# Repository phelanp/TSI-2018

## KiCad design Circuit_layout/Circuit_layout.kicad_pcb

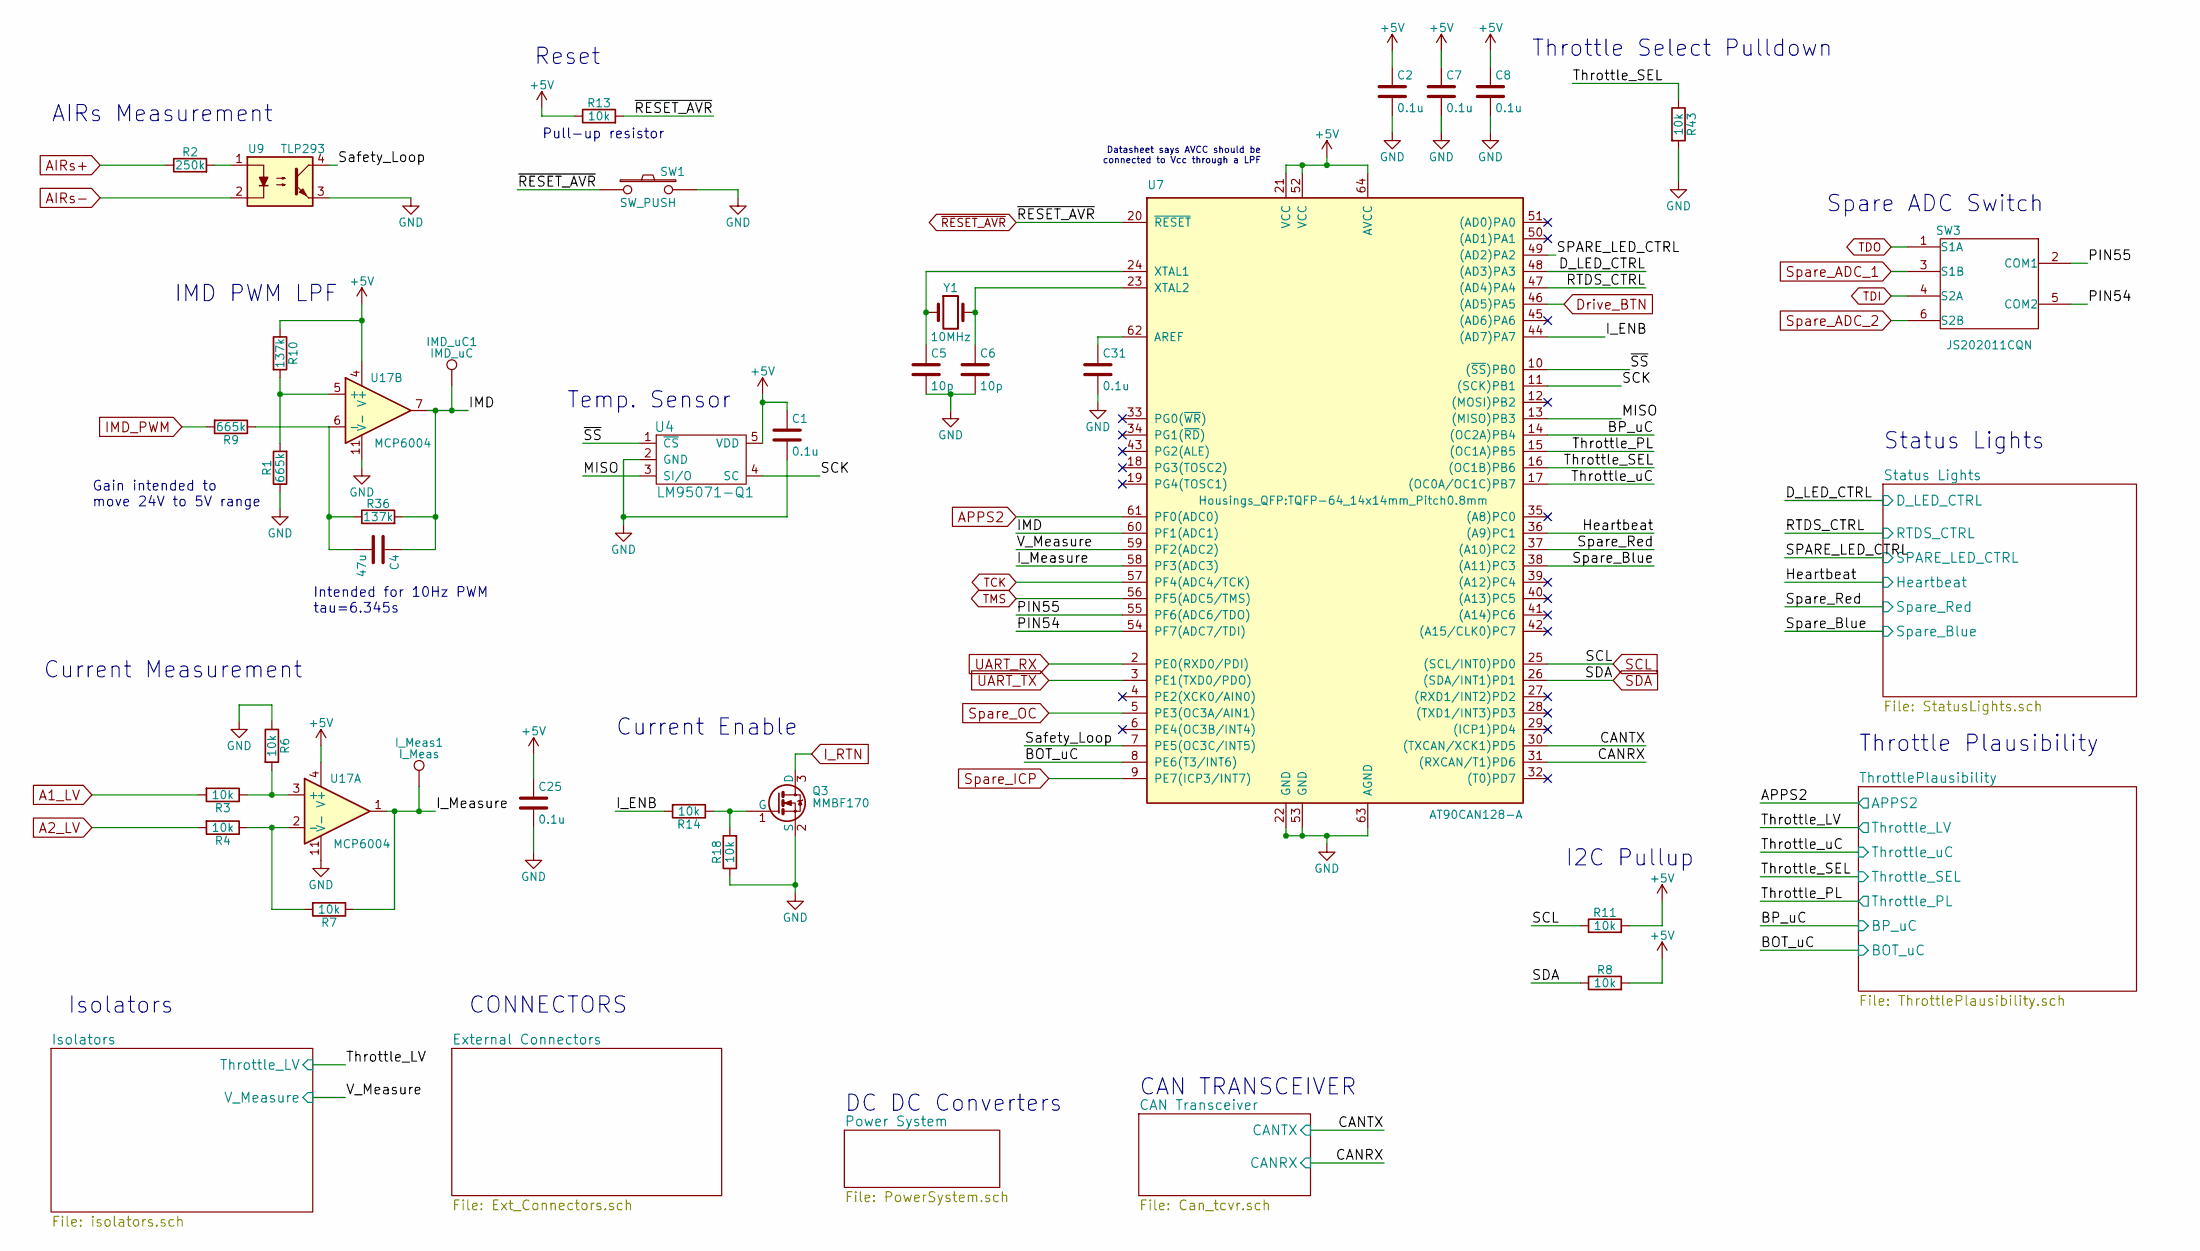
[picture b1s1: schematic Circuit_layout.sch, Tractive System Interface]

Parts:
C1, C2, C7, C8, C25, C31: 0.1u; C_0805_HandSoldering; Digikey P/N 399-1168-1-ND
C4: 47u; C_1210_HandSoldering; Digikey P/N 490-6538-1-ND
C5, C6: 10p; C_0805_HandSoldering; DigiKey P/N 399-1108-1-ND
IMD_uC1: IMD_uC; Measurement_Point_Round-SMD-Pad_Big
I_Meas1: I_Meas; Measurement_Point_Round-SMD-Pad_Big
Q3: MMBF170; SOT-23; Digikey P/N MMBF170CT-ND
R1, R9: 665k; R_0805_HandSoldering; DigiKey P/N P665KCCT-ND
R2: 250k; R_0805_HandSoldering; DigiKey P/N P249KCCT-ND
R3, R4, R6, R7, R8, R11, R13, R14, R18, R43: 10k; R_0805_HandSoldering; DigiKey P/N P10.0KCCT-ND
R10, R36: 137k; R_0805_HandSoldering; DigiKey P/N P137KCCT-ND
SW1: SW_PUSH; SW_RACON_8; DigiKey P/N 1715-1676-1-ND
SW3: JS202011CQN; CK_DPDT_Switch; DigiKey P/N 401-2001-ND
U4: LM95071-Q1; SOT-23-5_HandSoldering; DigiKey P/N 296-40259-1-ND
U7: AT90CAN128-A; TQFP-64_14x14mm_Pitch0.8mm; DigiKey P/N AT90CAN128-16AURCT-ND
U9: TLP293; SOP-4_4.4x2.8mm_Pitch1.27mm; DigiKey P/N TLP293(GB-TPLECT-ND
U17: MCP6004; SOIC-14_3.9x8.7mm_Pitch1.27mm; Digikey P/N MCP6004T-I/SLCT-ND
Y1: 10MHz; crystal_TXC_7A; DigiKey P/N 887-1741-1-ND

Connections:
+5V: C1.1, C2.1, C7.1, C8.1, C25.1, R8.2, R10.1, R11.2, R13.1, U4.5 (VDD), U7.21 (VCC), U7.52 (VCC), U7.64 (AVCC), U17.4 (V+); also elsewhere on the board
/BP_uC: U7.14 ((OC2A)PB4); also elsewhere on the board
/CANRX: U7.31 ((RXCAN/T1)PD6); also elsewhere on the board
/CANTX: U7.30 ((TXCAN/XCK1)PD5); also elsewhere on the board
/D_LED_CTRL: U7.48 ((AD3)PA3); also elsewhere on the board
/Heartbeat: U7.36 ((A9)PC1); also elsewhere on the board
/IMD: C4.1, IMD_uC1.1, R36.2, U7.60 (PF1(ADC1)), U17.7
/I_ENB: R14.2, U7.44 ((AD7)PA7)
/I_Measure: I_Meas1.1, R7.1, U7.58 (PF3(ADC3)), U17.1
/MISO: U4.3 (SI/O), U7.13 ((MISO)PB3)
/PIN54: SW3.5 (COM2), U7.54 (PF7(ADC7/TDI))
/PIN55: SW3.2 (COM1), U7.55 (PF6(ADC6/TDO))
/RTDS_CTRL: U7.47 ((AD4)PA4); also elsewhere on the board
/SCK: U4.4 (SC), U7.11 ((SCK)PB1)
/SPARE_LED_CTRL: U7.49 ((AD2)PA2); also elsewhere on the board
/Safety_Loop: U7.7 (PE5(OC3C/INT5)), U9.4
/Spare_Blue: U7.38 ((A11)PC3); also elsewhere on the board
/Spare_Red: U7.37 ((A10)PC2); also elsewhere on the board
/Throttle_PL: U7.15 ((OC1A)PB5); also elsewhere on the board
/Throttle_SEL: R43.1, U7.16 ((OC1B)PB6); also elsewhere on the board
/Throttle_uC: U7.17 ((OC0A/OC1C)PB7); also elsewhere on the board
/V_Measure: U7.59 (PF2(ADC2)); also elsewhere on the board
/~SS: U4.1 (~CS), U7.10 ((~SS~)PB0)
A1_LV: R3.2; also elsewhere on the board
A2_LV: R4.2; also elsewhere on the board
AIRs+: R2.1; also elsewhere on the board
AIRs-: U9.2; also elsewhere on the board
APPS2: U7.61 (PF0(ADC0)); also elsewhere on the board
CH_GND: C1.2, C2.2, C5.2, C6.2, C7.2, C8.2, C25.2, C31.2, Q3.2 (S), R1.1, R6.1, R18.1, R43.2, SW1.2, U4.2 (GND), U7.22 (GND), U7.53 (GND), U7.63 (AGND), U9.3, U17.11 (V-); also elsewhere on the board
Drive_BTN: U7.46 ((AD5)PA5); also elsewhere on the board
IMD_PWM: R9.2; also elsewhere on the board
I_RTN: Q3.3 (D); also elsewhere on the board
unnamed: C4.2, R9.1, R36.1, U17.6 (-)
unnamed: C5.1, U7.24 (XTAL1), Y1.1
unnamed: C6.1, U7.23 (XTAL2), Y1.2
unnamed: C31.1, U7.62 (AREF)
unnamed: Q3.1 (G), R14.1, R18.2
unnamed: R1.2, R10.2, U17.5 (+)
unnamed: R2.2, U9.1
unnamed: R3.1, R6.2, U17.3 (+)
unnamed: R4.1, R7.2, U17.2 (-)
SCL: R11.1, U7.25 ((SCL/INT0)PD0); also elsewhere on the board
SDA: R8.1, U7.26 ((SDA/INT1)PD1); also elsewhere on the board
Spare_ADC_1: SW3.3 (S1B); also elsewhere on the board
Spare_ADC_2: SW3.6 (S2B); also elsewhere on the board
Spare_ICP: U7.9 (PE7(ICP3/INT7)); also elsewhere on the board
Spare_OC: U7.5 (PE3(OC3A/AIN1)); also elsewhere on the board
TCK: U7.57 (PF4(ADC4/TCK)); also elsewhere on the board
TDI: SW3.4 (S2A); also elsewhere on the board
TDO: SW3.1 (S1A); also elsewhere on the board
TMS: U7.56 (PF5(ADC5/TMS)); also elsewhere on the board
UART_RX: U7.2 (PE0(RXD0/PDI)); also elsewhere on the board
UART_TX: U7.3 (PE1(TXD0/PDO)); also elsewhere on the board
~RESET_AVR: R13.2, SW1.1, U7.20 (~RESET); also elsewhere on the board

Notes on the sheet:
CONNECTORS
CAN TRANSCEIVER
Current Measurement
IMD PWM LPF
AIRs Measurement
Throttle Plausibility
Status Lights
DC DC Converters
Isolators
Intended for 10Hz PWM tau=6.345s
I2C Pullup
Datasheet says AVCC should be connected to Vcc through a LPF
Pull-up resistor
Reset
Throttle Select Pulldown
Spare ADC Switch
Current Enable
Gain intended to move 24V to 5V range
Temp. Sensor

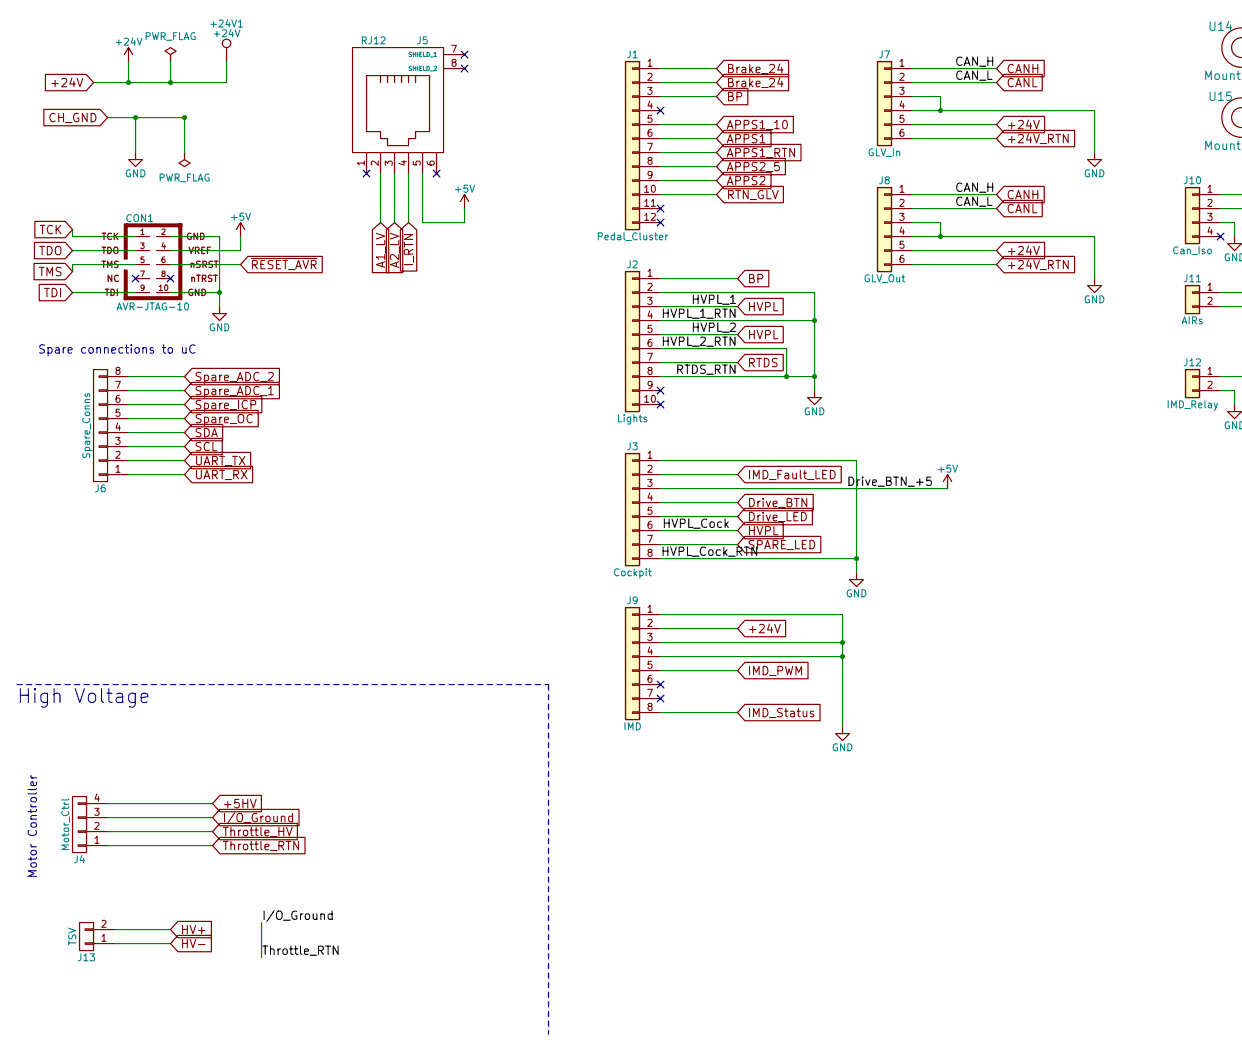
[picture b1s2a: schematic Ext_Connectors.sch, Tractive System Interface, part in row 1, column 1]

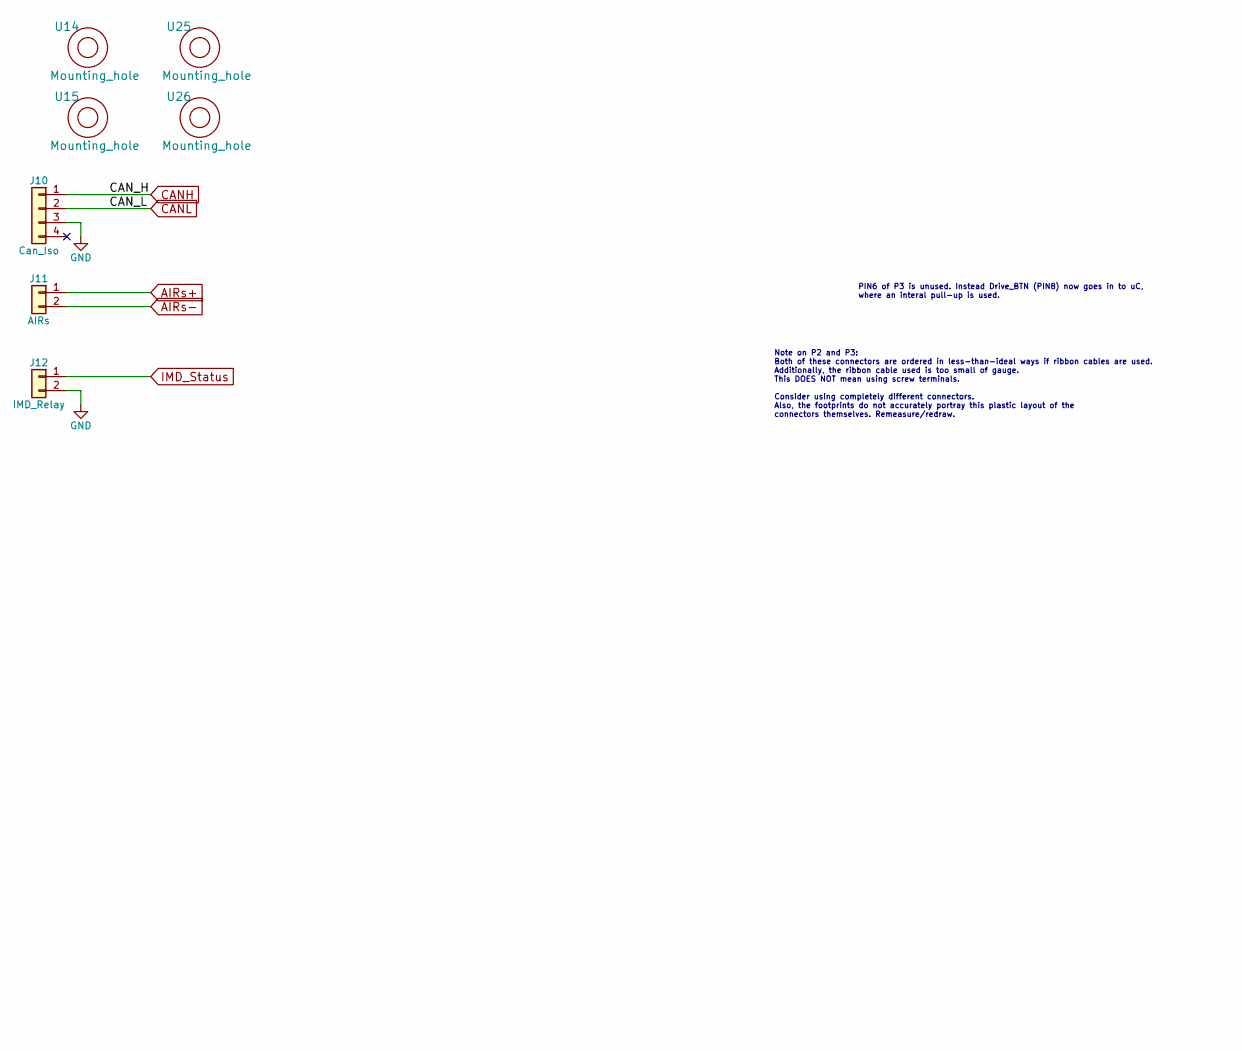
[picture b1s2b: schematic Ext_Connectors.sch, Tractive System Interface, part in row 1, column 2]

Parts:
+24V1: +24V; Measurement_Point_Round-SMD-Pad_Big
CON1: AVR-JTAG-10; JTAG; DigiKey P/N 609-4054-ND
J1: Pedal_Cluster; Molex_MiniFit-JR-5556-12A_2x06x4.20mm_Straight
J2: Lights; Molex_MiniFit-JR-5556-10A_2x05x4.20mm_Straight
J3: Cockpit; Molex_MiniFit-JR-5556-08A_2x04x4.20mm_Straight
J4: Motor_Ctrl; Molex_4x1_2.54mm; DigiKey P/N WM4802-ND
J5: RJ12; MOLEX_RJ11; DigiKey P/N WM3789CT-ND
J6: Spare_Conns; Molex_8x1_2.54mm; DigiKey P/N WM4128-ND
J7: GLV_In; Molex_MiniFit-JR-5556-06A_2x03x4.20mm_Straight
J8: GLV_Out; Molex_MiniFit-JR-5556-06A_2x03x4.20mm_Straight
J9: IMD; IMD_Header
J10: Can_Iso; Molex_MiniFit-JR-5556-04A_2x02x4.20mm_Straight
J11: AIRs; Molex_MiniFit-JR-5556-02A_2x01x4.20mm_Straight
J12: IMD_Relay; Molex_MiniFit-JR-5556-02A_2x01x4.20mm_Straight
J13: TSV; AMPCONN_2; DigiKey P/N A113980-ND
U14, U15, U25, U26: Mounting_hole; MountingHole_3.5mm_Pad

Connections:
+5HV: J4.4; also elsewhere on the board
+5V: CON1.4, J3.3, J5.5; also elsewhere on the board
+24V: +24V1.1, J1.1, J1.2, J7.5, J8.5, J9.2; also elsewhere on the board
+24V_RTN: J7.6, J8.6; also elsewhere on the board
A1_LV: J5.2; also elsewhere on the board
A2_LV: J5.3; also elsewhere on the board
AIRs+: J11.1; also elsewhere on the board
AIRs-: J11.2; also elsewhere on the board
APPS1: J1.6; also elsewhere on the board
APPS1_10: J1.5; also elsewhere on the board
APPS1_RTN: J1.7; also elsewhere on the board
APPS2: J1.9; also elsewhere on the board
APPS2_5: J1.8; also elsewhere on the board
BP: J1.3, J2.1; also elsewhere on the board
CANH: J7.1, J8.1, J10.1; also elsewhere on the board
CANL: J7.2, J8.2, J10.2; also elsewhere on the board
CH_GND: CON1.2, CON1.10, J1.10, J2.2, J2.4, J2.6, J2.8, J3.1, J3.8, J7.3, J7.4, J8.3, J8.4, J9.1, J9.3, J9.4, J10.3, J12.2; also elsewhere on the board
Drive_BTN: J3.4; also elsewhere on the board
Drive_LED: J3.5; also elsewhere on the board
HV+: J13.2; also elsewhere on the board
HV-: J13.1; also elsewhere on the board
HVPL: J2.3, J2.5, J3.6; also elsewhere on the board
I/O_Ground: J4.1, J4.3; also elsewhere on the board
IMD_Fault_LED: J3.2; also elsewhere on the board
IMD_PWM: J9.5; also elsewhere on the board
IMD_Status: J9.8, J12.1; also elsewhere on the board
I_RTN: J5.4; also elsewhere on the board
RTDS: J2.7; also elsewhere on the board
SCL: J6.3; also elsewhere on the board
SDA: J6.4; also elsewhere on the board
SPARE_LED: J3.7; also elsewhere on the board
Spare_ADC_1: J6.7; also elsewhere on the board
Spare_ADC_2: J6.8; also elsewhere on the board
Spare_ICP: J6.6; also elsewhere on the board
Spare_OC: J6.5; also elsewhere on the board
TCK: CON1.1; also elsewhere on the board
TDI: CON1.9; also elsewhere on the board
TDO: CON1.3; also elsewhere on the board
TMS: CON1.5; also elsewhere on the board
Throttle_HV: J4.2; also elsewhere on the board
UART_RX: J6.1; also elsewhere on the board
UART_TX: J6.2; also elsewhere on the board
~RESET_AVR: CON1.6; also elsewhere on the board

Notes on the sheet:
Motor Controller
High Voltage
Spare connections to uC
PIN6 of P3 is unused. Instead Drive_BTN (PIN8) now goes in to uC, where an interal pull-up is used.
Note on P2 and P3: Both of these connectors are ordered in less-than-ideal ways if ribbon cables are used. Additionally, the ribbon cable used is too small of gauge. This DOES NOT mean using screw terminals. Consider using completely different connectors. Also, the footprints do not accurately port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

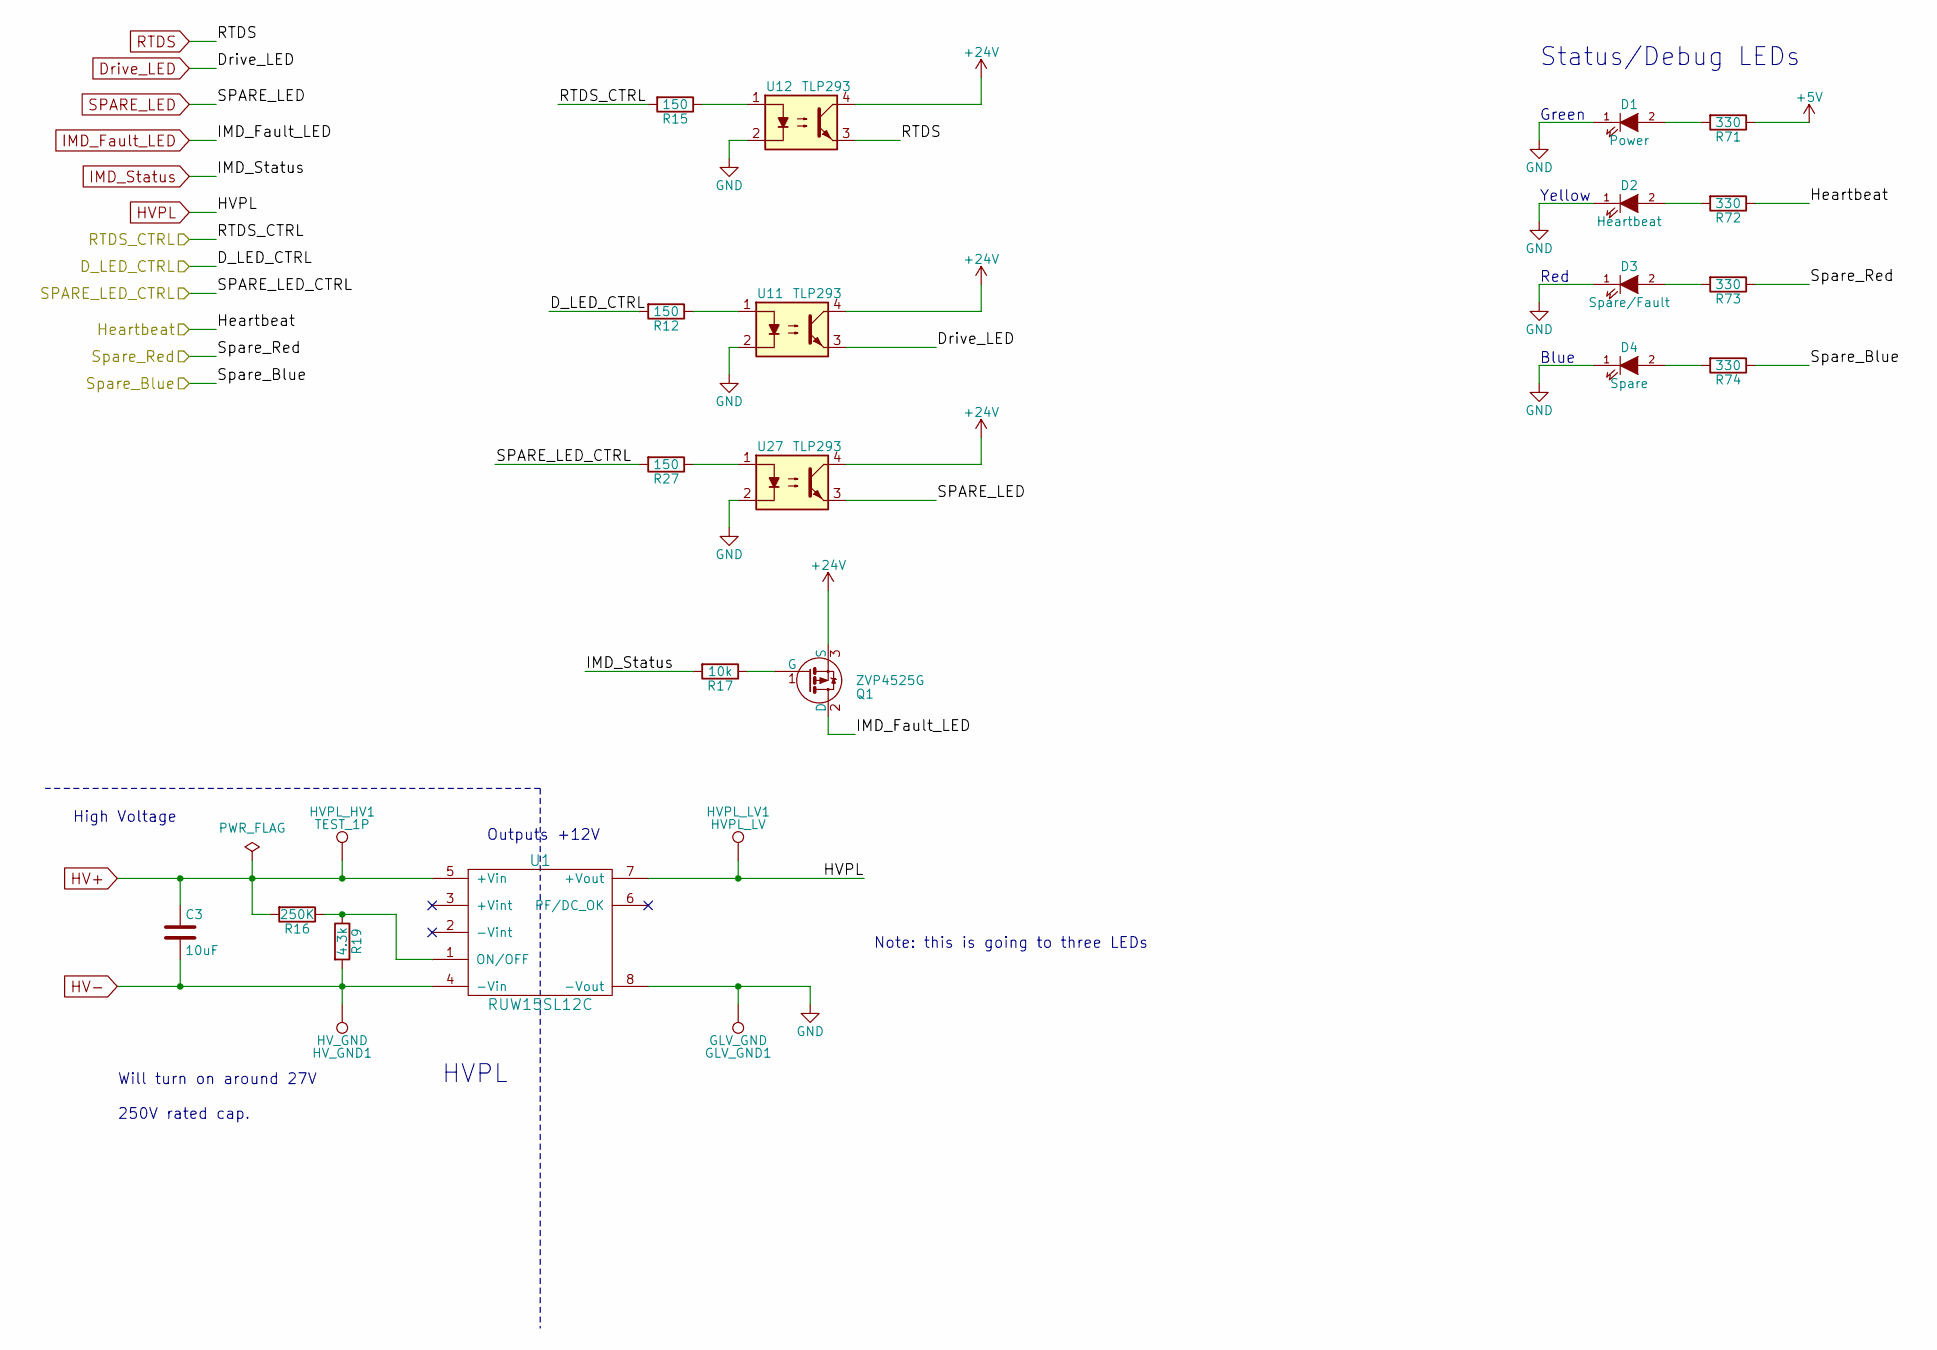
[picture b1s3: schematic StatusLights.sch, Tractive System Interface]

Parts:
C3: 10uF; CP_Radial_D10.0mm_P5.00mm; DigiKey P/N 490-3550-1-ND
D1: Power; LED_0805; DigiKey P/N 475-1410-1-ND
D2: Heartbeat; LED_0805; DigiKey P/N 475-2560-1-ND
D3: Spare/Fault; LED_0805; DigiKey P/N 475-1278-1-ND
D4: Spare; LED_0805; DigiKey P/N 516-1445-1-ND
GLV_GND1: GLV_GND; Measurement_Point_Square-SMD-Pad_Big
HVPL_HV1: TEST_1P; Measurement_Point_Round-SMD-Pad_Big
HVPL_LV1: HVPL_LV; Measurement_Point_Round-SMD-Pad_Big
HV_GND1: HV_GND; Measurement_Point_Square-SMD-Pad_Big
Q1: ZVP4525G; SOT-223-3Lead_TabPin2; DigiKey P/N ZVP4525GCT-ND
R12, R15, R27: 150; R_0805_HandSoldering; DigiKey P/N 311-150CRCT-ND
R16: 250K; R_0805_HandSoldering
R17: 10k; R_0805_HandSoldering; DigiKey P/N P10.0KCCT-ND
R19: 4.3k; R_0805_HandSoldering
R71, R72, R73, R74: 330; R_0805_HandSoldering; DigiKey P/N P330CCT-ND
U1: RUW15SL12C; RUW15
U11, U12, U27: TLP293; SOP-4_4.4x2.8mm_Pitch1.27mm; DigiKey P/N TLP293(GB-TPLECT-ND

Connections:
+5V: R71.1; also elsewhere on the board
+24V: Q1.3 (S), U11.4, U12.4, U27.4; also elsewhere on the board
/D_LED_CTRL: R12.2; also elsewhere on the board
/Heartbeat: R72.1; also elsewhere on the board
/RTDS_CTRL: R15.2; also elsewhere on the board
/SPARE_LED_CTRL: R27.2; also elsewhere on the board
/Spare_Blue: R74.1; also elsewhere on the board
/Spare_Red: R73.1; also elsewhere on the board
CH_GND: D1.1 (K), D2.1 (K), D3.1 (K), D4.1 (K), GLV_GND1.1, U1.8 (-Vout), U11.2, U12.2, U27.2; also elsewhere on the board
Drive_LED: U11.3; also elsewhere on the board
HV+: C3.1, HVPL_HV1.1, R16.2, U1.5 (+Vin); also elsewhere on the board
HV-: C3.2, HV_GND1.1, R19.2, U1.4 (-Vin); also elsewhere on the board
HVPL: HVPL_LV1.1, U1.7 (+Vout); also elsewhere on the board
IMD_Fault_LED: Q1.2 (D); also elsewhere on the board
IMD_Status: R17.2; also elsewhere on the board
unnamed: D1.2 (A), R71.2
unnamed: D2.2 (A), R72.2
unnamed: D3.2 (A), R73.2
unnamed: D4.2 (A), R74.2
unnamed: Q1.1 (G), R17.1
unnamed: R12.1, U11.1
unnamed: R15.1, U12.1
unnamed: R16.1, R19.1, U1.1 (ON/OFF)
unnamed: R27.1, U27.1
RTDS: U12.3; also elsewhere on the board
SPARE_LED: U27.3; also elsewhere on the board

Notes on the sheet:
Green
Yellow
Red
Blue
Status/Debug LEDs
High Voltage
Note: this is going to three LEDs
Outputs +12V
HVPL
Will turn on around 27V 250V rated cap.

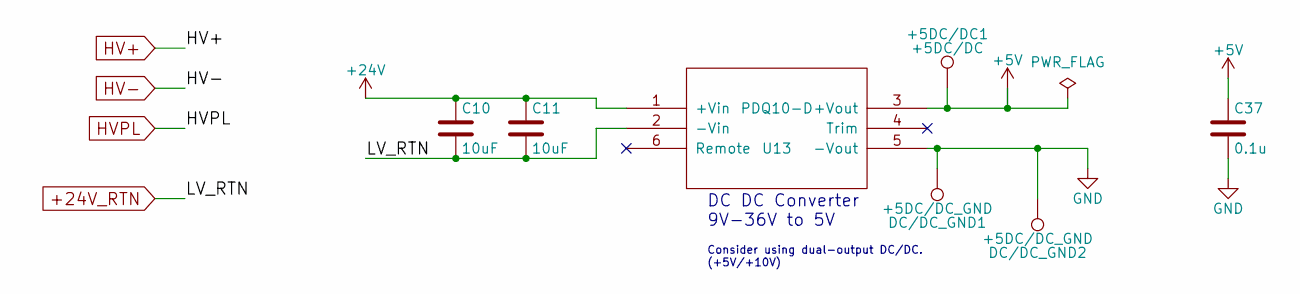
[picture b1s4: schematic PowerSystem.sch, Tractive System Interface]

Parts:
+5DC/DC1: +5DC/DC; trim_pot
C10, C11: 10uF; C_0805_HandSoldering; DigiKey P/N 490-10515-1-ND
C37: 0.1u; C_0805_HandSoldering; Digikey P/N 399-1168-1-ND
DC/DC_GND1, DC/DC_GND2: +5DC/DC_GND; Measurement_Point_Square-SMD-Pad_Big
U13: PDQ10-D; PDQ_DCDC; DigiKey P/N 102-3865-ND

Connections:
+5V: +5DC/DC1.1, C37.1, U13.3 (+Vout); also elsewhere on the board
+24V: C10.1, C11.1, U13.1 (+Vin); also elsewhere on the board
+24V_RTN: C10.2, C11.2, U13.2 (-Vin); also elsewhere on the board
CH_GND: C37.2, DC/DC_GND1.1, DC/DC_GND2.1, U13.5 (-Vout); also elsewhere on the board

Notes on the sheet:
DC DC Converter 9V-36V to 5V
Consider using dual-output DC/DC. (+5V/+10V)

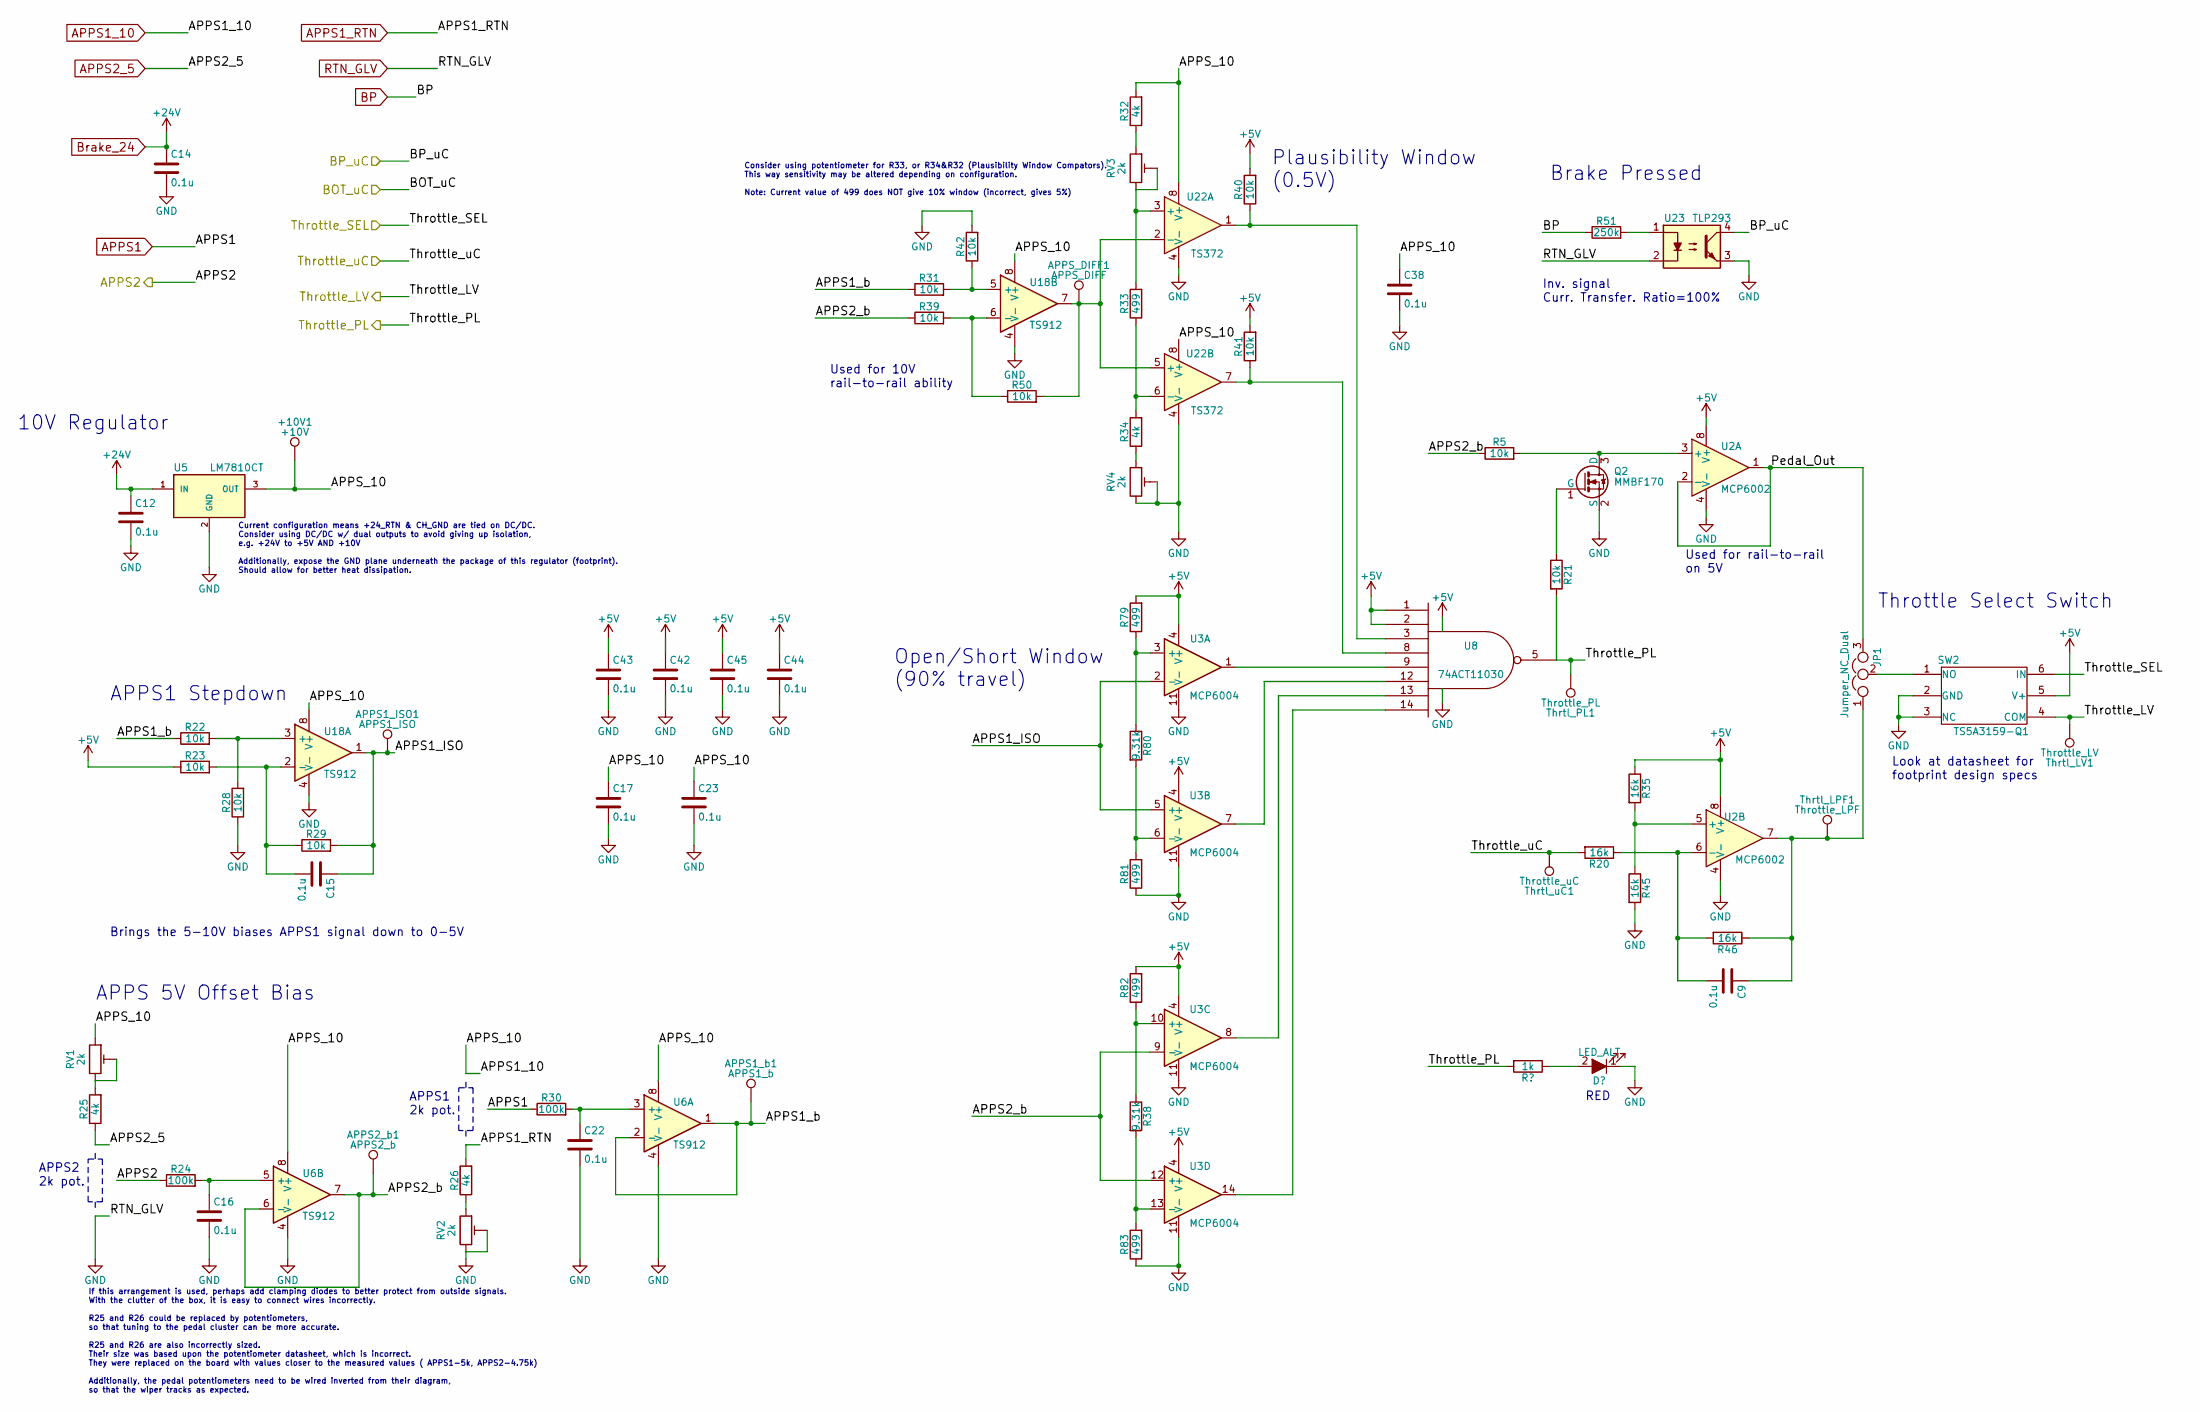
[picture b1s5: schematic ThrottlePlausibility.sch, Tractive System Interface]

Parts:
+10V1: +10V; Measurement_Point_Round-SMD-Pad_Big
APPS1_ISO1: APPS1_ISO; Measurement_Point_Round-SMD-Pad_Big
APPS1_b1: APPS1_b; Measurement_Point_Round-SMD-Pad_Big
APPS2_b1: APPS2_b; Measurement_Point_Round-SMD-Pad_Big
APPS_DIFF1: APPS_DIFF; Measurement_Point_Round-SMD-Pad_Big
C9, C12, C14, C15, C16, C17, C22, C23, C38, C42, C43, C44, C45: 0.1u; C_0805_HandSoldering; Digikey P/N 399-1168-1-ND
JP1: Jumper_NC_Dual; Pin_Header_Straight_1x03_Pitch2.54mm
Q2: MMBF170; SOT-23; Digikey P/N MMBF170CT-ND
R5, R21, R22, R23, R28, R29, R31, R39, R40, R41, R42, R50: 10k; R_0805_HandSoldering; DigiKey P/N P10.0KCCT-ND
R20, R35, R45, R46: 16k; R_0805_HandSoldering; DigiKey P/N P10.0KCCT-ND
R24, R30: 100k; R_0805_HandSoldering; DigiKey P/N P100KCCT-ND
R25, R26: 4k; R_0805_HandSoldering; DigiKey P/N P2.00KCCT-ND
R32, R34: 4k; R_0805_HandSoldering; DigiKey P/N P4.75KCCT-ND
R33, R79, R81, R82, R83: 499; R_0805_HandSoldering; DigiKey P/N P499DACT-ND
R38, R80: 9.31k; R_0805_HandSoldering; Digikey P/N P9.31KCCT-ND
R51: 250k; R_0805_HandSoldering; DigiKey P/N P249KCCT-ND
RV1, RV2, RV3, RV4: 2k; trim_pot
SW2: TS5A3159-Q1; SOT-23-6_Handsoldering; DigiKey P/N 296-39512-1-ND
Thrtl_LPF1: Throttle_LPF; Measurement_Point_Square-SMD-Pad_Big
Thrtl_LV1: Throttle_LV; Measurement_Point_Round-SMD-Pad_Big
Thrtl_PL1: Throttle_PL; Measurement_Point_Round-SMD-Pad_Big
Thrtl_uC1: Throttle_uC; Measurement_Point_Square-SMD-Pad_Big
U2: MCP6002; SOIC-8_3.9x4.9mm_Pitch1.27mm; DigiKey P/N MCP6002T-I/SNCT-ND
U3: MCP6004; SOIC-14_3.9x8.7mm_Pitch1.27mm; Digikey P/N MCP6004T-I/SLCT-ND
U5: LM7810CT; TO-220_Horizontal_Plated_Hole; DigiKey P/N LM7810CT-ND
U6, U18: TS912; SOIC-8_3.9x4.9mm_Pitch1.27mm; DigiKey P/N 497-10252-1-ND
U8: 74ACT11030; SOIC-14_3.9x8.7mm_Pitch1.27mm; Digikey P/N 296-4180-1-ND
U22: TS372; SOIC-8_3.9x4.9mm_Pitch1.27mm; DigiKey P/N 497-2271-1-ND
U23: TLP293; SOP-4_4.4x2.8mm_Pitch1.27mm; DigiKey P/N TLP293(GB-TPLECT-ND

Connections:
+5V: C42.1, C43.1, C44.1, C45.1, R23.1, R35.1, R40.2, R41.2, R79.2, R82.2, SW2.5 (V+), U2.8 (V+), U3.4 (V+), U8.1, U8.2, U8.11 (VCC); also elsewhere on the board
+24V: C12.1, C14.1, U5.1 (IN); also elsewhere on the board
/BP_uC: U23.4; also elsewhere on the board
/ThrottlePlausibility/APPS1_ISO: APPS1_ISO1.1, C15.1, R29.2, U3.2 (-), U3.5 (+), U18.1
/ThrottlePlausibility/APPS1_b: APPS1_b1.1, R22.1, R31.1, U6.1, U6.2 (-)
/ThrottlePlausibility/APPS2_b: APPS2_b1.1, R5.1, R39.1, U3.9 (-), U3.12 (+), U6.6 (-), U6.7
/ThrottlePlausibility/Pedal_Out: JP1.3, U2.1, U2.2 (-)
/Throttle_LV: SW2.4 (COM), Thrtl_LV1.1; also elsewhere on the board
/Throttle_PL: R21.2, Thrtl_PL1.1, U8.5; also elsewhere on the board
/Throttle_SEL: SW2.6 (IN); also elsewhere on the board
/Throttle_uC: R20.2, Thrtl_uC1.1; also elsewhere on the board
APPS1: R30.1; also elsewhere on the board
APPS1_10: +10V1.1, C17.1, C23.1, C38.1, R32.2, RV1.1, U5.3 (OUT), U6.8 (V+), U18.8 (V+), U22.8 (V+); also elsewhere on the board
APPS1_RTN: R26.2; also elsewhere on the board
APPS2: R24.1; also elsewhere on the board
APPS2_5: R25.1; also elsewhere on the board
BP: R51.1; also elsewhere on the board
CH_GND: C12.2, C14.2, C16.2, C17.2, C22.2, C23.2, C38.2, C42.2, C43.2, C44.2, C45.2, Q2.2 (S), R28.1, R42.2, R45.2, R81.1, R83.1, RV2.2, RV2.3, RV4.2, RV4.3, SW2.2 (GND), SW2.3 (NC), U2.4 (V-), U3.11 (V-), U5.0 (GND), U5.2 (GND), U6.4 (V-), U8.4 (GND), U18.4 (V-), U22.4 (V-), U23.2, U23.3; also elsewhere on the board
unnamed: APPS_DIFF1.1, R50.2, U18.7, U22.2 (-), U22.5 (+)
unnamed: C9.1, JP1.1, R46.1, Thrtl_LPF1.1, U2.7
unnamed: C9.2, R20.1, R46.2, U2.6 (-)
unnamed: C15.2, R23.2, R29.1, U18.2 (-)
unnamed: C16.1, R24.2, U6.5 (+)
unnamed: C22.1, R30.2, U6.3 (+)
unnamed: JP1.2, SW2.1 (NO)
unnamed: Q2.1 (G), R21.1
unnamed: Q2.3 (D), R5.2, U2.3 (+)
unnamed: R22.2, R28.2, U18.3 (+)
unnamed: R25.2, RV1.2, RV1.3
unnamed: R26.1, RV2.1
unnamed: R31.2, R42.1, U18.5 (+)
unnamed: R32.1, RV3.1
unnamed: R33.1, R34.2, U22.6 (-)
unnamed: R33.2, RV3.2, RV3.3, U22.3 (+)
unnamed: R34.1, RV4.1
unnamed: R35.2, R45.1, U2.5 (+)
unnamed: R38.1, R82.1, U3.10 (+)
unnamed: R38.2, R83.2, U3.13 (-)
unnamed: R39.2, R50.1, U18.6 (-)
unnamed: R40.1, U8.3, U22.1
unnamed: R41.1, U8.8, U22.7
unnamed: R51.2, U23.1
unnamed: R79.1, R80.1, U3.3 (+)
unnamed: R80.2, R81.2, U3.6 (-)
unnamed: U3.1, U8.9
unnamed: U3.7, U8.12
unnamed: U3.8, U8.13
unnamed: U3.14, U8.14

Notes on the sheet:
Used for 10V rail-to-rail ability
Used for rail-to-rail on 5V
Plausibility Window (0.5V)
Brake Pressed
Open/Short Window (90% travel)
APPS2 2k pot.
APPS1 2k pot.
Inv. signal Curr. Transfer. Ratio=100%
APPS 5V Offset Bias
Look at datasheet for footprint design specs
Consider using potentiometer for R33, or R34&R32 (Plausibility Window Compators). This way sensitivity may be altered depending on configuration. Note: Current value of 499 does NOT give 10% window (incorrect, gives 5%)
Current configuration means +24_RTN & CH_GND are tied on DC/DC. Consider using DC/DC w/ dual outputs to avoid giving up isolation, e.g. +24V to +5V AND +10V Additionally, expose the GND plane underneath the package of this regulator (footprint). Should allow for better heat dissipation.
If this arrangement is used, perhaps add clamping diodes to better protect from outside signals. With the clutter of the box, it is easy to connect wires incorrectly. R25 and R26 could be replaced by potentiometers, so that tuning to the pedal cluster can be more accurate. R25 and R26 are also inco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
APPS1 Stepdown
Brings the 5-10V biases APPS1 signal down to 0-5V
10V Regulator
Throttle Select Switch
RED
